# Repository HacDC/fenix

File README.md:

# Franken-Fenix

[![Nix
formatting](https://github.com/HacDC/fenix/actions/workflows/nix-fmt.yml/badge.svg)](https://github.com/HacDC/fenix/actions/workflows/nix-fmt.yml)

[HacDC's Spaceblimp VIII](https://wiki.hacdc.org/en/Projects/spaceblimp/Space-Blimp)

# Supported Development Platforms

In theory it shouldn't really matter what operating system your computer
uses. This may or may not be the case in practice:

* Ubuntu: works

* MacOS: Doesn't work: arm issue

* Windows Subsystem for Linux: Operational (at least with Ubuntu noble)

* NixOS: Does not work (NixOS/nixpkgs#372653). Ivan is trying to find a
  workaround that we can use until the proper fix is merged
  (NixOS/nixpkgs#477552).

# Setup

1. If you haven't already done so, you must first install Nix. The official
   installation guide can be found here: https://nix.dev/install-nix

2. Any time you open a new terminal window, you will need to run
   `nix develop`.

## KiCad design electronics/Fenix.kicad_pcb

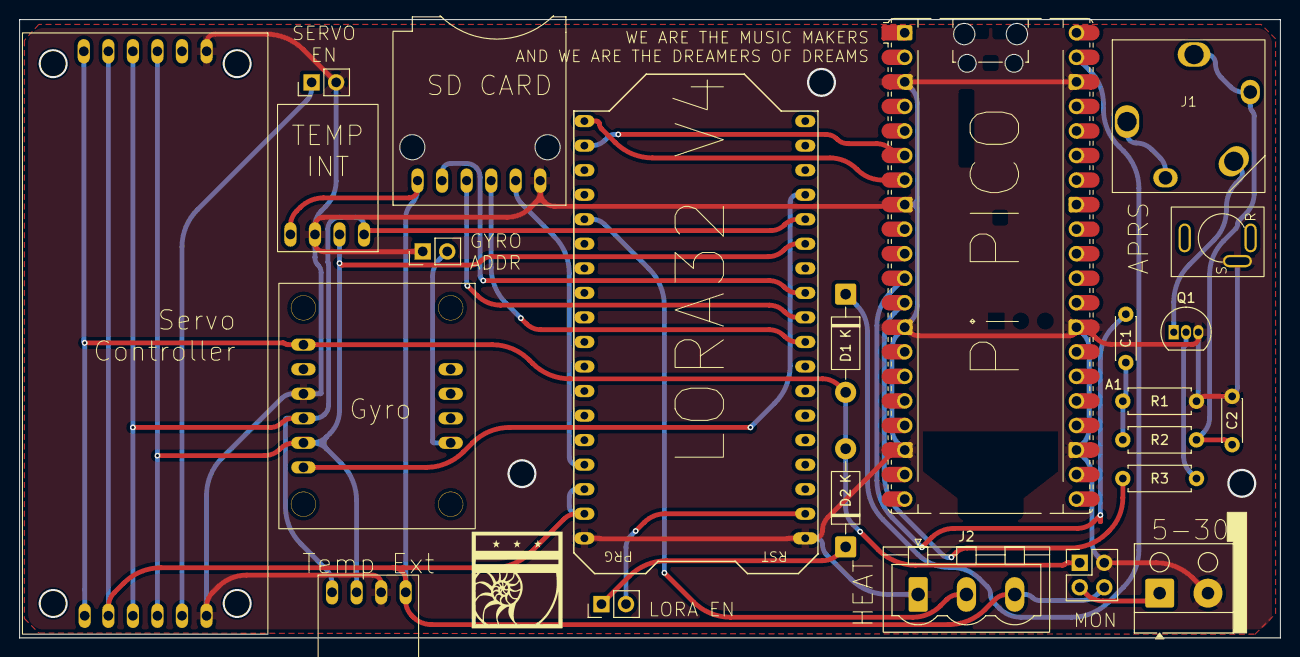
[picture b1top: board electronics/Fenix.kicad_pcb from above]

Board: 2 copper layers, 130.5 x 64.0 mm, 23 parts (0 on the bottom side), 25 nets.

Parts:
A1: RaspberryPi_Pico; RaspberryPi_Pico_Common_Unspecified
C1: 100nF; C_Disc_D4.3mm_W1.9mm_P5.00mm
C2: 4.7nF; C_Disc_D4.3mm_W1.9mm_P5.00mm
D1, D2: 1N5817; D_DO-41_SOD81_P10.16mm_Horizontal
Gyro1: Adafruit_BNO055
J1: Radio 3.5mm; TRS_3.5mm
J2: Relay_Control; PhoenixContact_MSTBVA_2,5_3-G_1x03_P5.00mm_Vertical
J3: Radio 2.5mm; TRS_2.5mm
J3_ADR1, J4_LORA_PWR1, J4_SRV_EN1: Conn_01x02_Pin; PinHeader_1x02_P2.54mm_Vertical
J4: PWR_MON; PinHeader_2x02_P2.54mm_Vertical
J5: PWR_IN; Altech_AK100_1x02_P5.00mm
LoRa32_V1: LORA32_V4
Q1: BC548; TO-92_Inline
R1, R2: 4k7; R_Axial_DIN0207_L6.3mm_D2.5mm_P7.62mm_Horizontal
R3: 1k; R_Axial_DIN0207_L6.3mm_D2.5mm_P7.62mm_Horizontal
Servo_Controller1: Adafruit_PCA9685
TEMP_EXT1: GY-SHT31-D
TEMP_INT1: GY-SHT31-D
uSD1: Generic_uSD

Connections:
+3V3: J2.3, J4.4, LoRa32_V1.34 (3v3), LoRa32_V1.35 (3V3), Servo_Controller1.5 (VCC), Servo_Controller1.8 (VCC), TEMP_EXT1.1 (VIN), TEMP_INT1.1 (VIN), uSD1.1 (3V3)
+5V: D1.2 (A), D2.2 (A), Gyro1.1 (VIN), J4.1, Servo_Controller1.6 (V+), Servo_Controller1.7 (V+)
/APRS_3.5_Sleeve: J1.S, Q1.1 (C)
/APRS_RX: A1.6 (GPIO4), LoRa32_V1.20 (G06)
/APRS_TX: A1.7 (GPIO5), LoRa32_V1.19 (G07)
/GYRO_RST: Gyro1.6 (RST), LoRa32_V1.15 (G26)
/I2C_CLK: Gyro1.5 (SCL), LoRa32_V1.13 (G47), Servo_Controller1.3 (SCL), Servo_Controller1.10 (SCL), TEMP_EXT1.3 (SCL), TEMP_INT1.3 (SCL)
/I2C_DATA: Gyro1.4 (SDA), LoRa32_V1.14 (G48), Servo_Controller1.4 (SDA), Servo_Controller1.9 (SDA), TEMP_EXT1.4 (SDA), TEMP_INT1.4 (SDA)
/RELAY_EN: J2.2, LoRa32_V1.23 (G03)
/SPI_CLK: LoRa32_V1.09 (G36), uSD1.4 (CLK)
/SPI_CS_SD: LoRa32_V1.11 (G34), uSD1.2 (CS)
/SPI_PICO: LoRa32_V1.10 (G35), uSD1.3 (PICO)
/SPI_POCI: LoRa32_V1.33 (G37), uSD1.5 (POCI)
GND: A1.3 (GND), A1.8 (GND), A1.13 (GND), A1.18 (GND), A1.23 (GND), A1.28 (GND), A1.38 (GND), C2.2, Gyro1.3 (GND), J2.1, J3.S, J3_ADR1.1, J4.2, J4_SRV_EN1.2, J5.2, LoRa32_V1.01 (GND), LoRa32_V1.36 (GND), Q1.3 (E), R1.2, Servo_Controller1.1 (GND), Servo_Controller1.12 (GND), TEMP_EXT1.2 (GND), TEMP_INT1.2 (GND), uSD1.6 (GND)
unnamed: A1.11 (GPIO8), C1.2
unnamed: A1.12 (GPIO9), R3.2
unnamed: A1.39 (VSYS), D1.1 (K)
unnamed: C1.1, R1.1, R2.2
unnamed: C2.1, J1.R, R2.1
unnamed: D2.1 (K), J4_LORA_PWR1.1
unnamed: Gyro1.7 (ADR), J3_ADR1.2
unnamed: J4.3, J5.1
unnamed: J4_LORA_PWR1.2, LoRa32_V1.02 (5V)
unnamed: J4_SRV_EN1.1, Servo_Controller1.11 (OE)
unnamed: Q1.2 (B), R3.1

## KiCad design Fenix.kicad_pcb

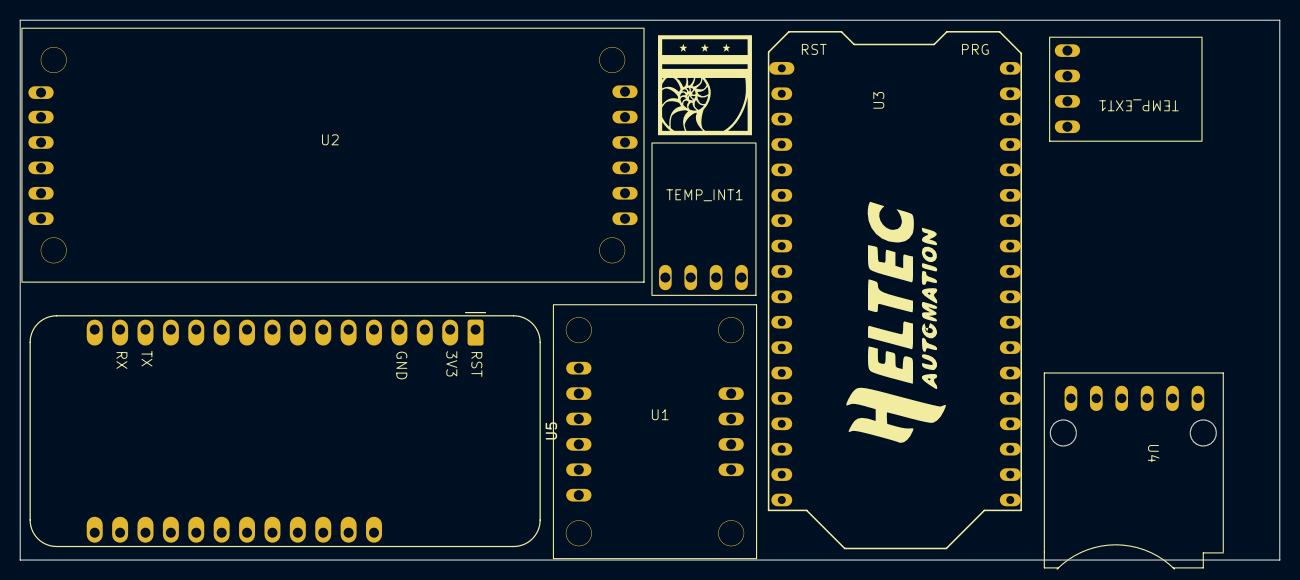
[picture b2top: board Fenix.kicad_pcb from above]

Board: 2 copper layers, 126.0 x 54.0 mm, 7 parts (0 on the bottom side), 3 nets, no tracks yet.

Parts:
TEMP_EXT1: GY-SHT31-D
TEMP_INT1: GY-SHT31-D
U1: Adafruit_BNO055
U2: Adafruit_PCA9685
U3: LORA32_V4
U4: Generic_uSD
U5: Adafruit_GPSFeather

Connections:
+3V3: U1.2 (3vo), U2.5 (VCC), U2.8 (VCC), U3.34 (3v3), U3.35 (3V3), U4.1 (3V3), U5.2 (3V3)
+5V: U2.6 (V+), U2.7 (V+)
GND: U1.3 (GND), U2.1 (GND), U2.12 (GND), U3.36 (GND), U4.6 (GND), U5.4 (GND)

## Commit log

2025-11-30 Core Parts
2025-12-01 Completed parts library
2025-12-12 Added ToDos in schematic
2025-12-15 Added uSD + Power connector
2025-12-15 Add 3dModel of Lora and remove silkscreen heltec
2026-01-06 Add Space-Blimp project link to README
    Added a link to the Space-Blimp project wiki on HacDC site.
2026-01-17 Create firmware instructions
2026-01-17 Generate blank rust project
2026-01-18 Generate ground-station project
2026-01-18 Regenerate ground-station project to comply with ASCII requirements
2026-01-19 Implement LoRa for ground station
2026-01-19 Cleanup KiCad leftovers
2026-01-19 Update Symbol/Footprint link & Remove GPS board
2026-01-19 Organize nets/symbols
2026-01-21 Complete RX/TX examples in the two firmwares
2026-01-23 Hardware Night: Finish schematic and PCB routing for known parts
2026-01-23 Add PCB Render
2026-01-26 Update moved link
2026-02-03 Switch to nix-based development environment
2026-02-03 design budget drafts
2026-02-04 Move firmware/fenix-rust/* to firmware/*
2026-02-04 Update flashing instructions
2026-02-04 Create modules for fenix and fraublucher
2026-02-04 Move fireware documentation to the correct README
2026-02-04 Generate core components
2026-02-05 Add very basic readmes for library components
2026-02-05 Remake libs in matching format
2026-02-05 Remove lock file
2026-02-05 Split LoRa out to library
2026-02-05 Add License + Project links
2026-02-05 implement TX ability
2026-02-05 Update ecan, cleanup
2026-02-06 Update README with MacOS and WSL status
2026-02-06 Increase log verbosity
2026-02-06 Ignore nix build artifacts
2026-02-06 Create a .rustfmt.toml file
    For now, I attempted to match the existing codestyle as best I can
    with just a few minutes work.
2026-02-06 Add prototype Github Action for building firmware
2026-02-06 Run `cargo fmt`
2026-02-06 Wow I can't spell
2026-02-06 attempt removal of nix-build
2026-02-06 Cleanup FenixLoRa.receive
2026-02-06 Nix shelly johnson
2026-02-06 PreRebase Commit
2026-02-07 I2C Scanner tool
2026-02-07 Add I2C bus
2026-02-07 WIP SD Card access
2026-02-10 A different failed attempt
2026-02-10 Tweak build settings
2026-02-10 Fix warnings about unused variables
2026-02-10 Run formatter
2026-02-10 Fix ownership errors
2026-02-10 Construct FenixSD
2026-02-10 Cleanup clippy lints
2026-02-10 Setup github actions
2026-02-10 Fixup status badge
2026-02-10 Fixup rust-ci.yml
2026-02-16 Start implementing servo support
2026-02-16 Adjust readme for build
2026-02-16 Fix merge with Ivan's servo work
2026-02-17 Fix CI failures
2026-02-18 APRS Schematic
2026-02-18 APRS Footprints
2026-02-19 Some PCB layout, will need to redo 3.5mm jack footprint
2026-02-19 Pre-Routing Board Layout
2026-02-19 Completed PCB Design
2026-02-24 Create separate Fenix Logging module
2026-02-24 Create a file for storing servo state
2026-03-16 Install vscode
2026-03-16 Enable wrapping for comments
2026-03-27 Install esptool
2026-03-27 Fix fenix crash thing
